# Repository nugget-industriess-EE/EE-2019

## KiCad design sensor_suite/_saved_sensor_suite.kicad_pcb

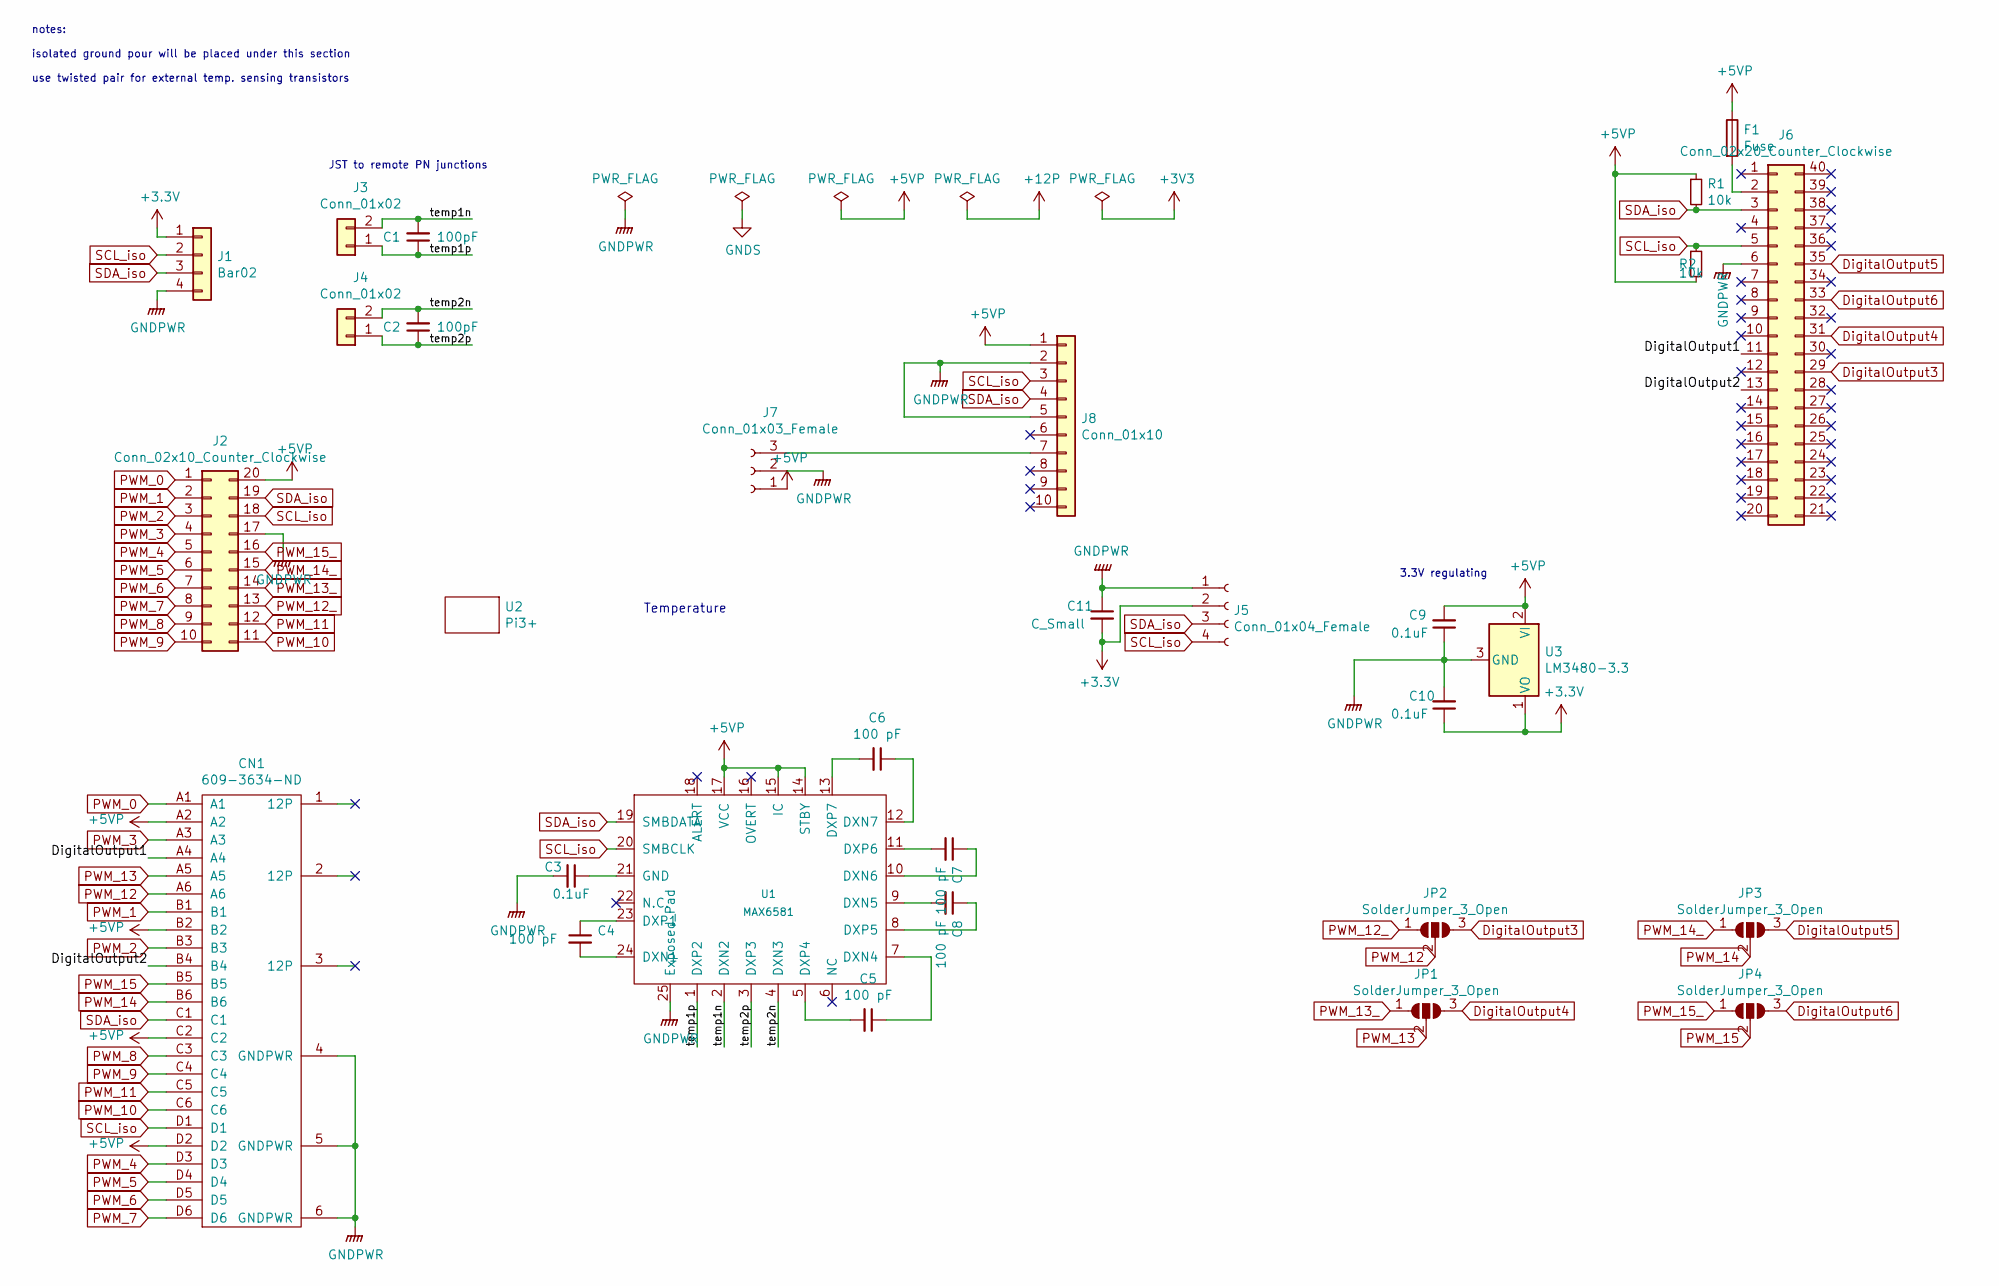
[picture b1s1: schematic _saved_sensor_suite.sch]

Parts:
C1, C2: 100pF; C_0805_2012Metric_Pad1.15x1.40mm_HandSolder
C3, C9, C10: 0.1uF; C_0805_2012Metric_Pad1.15x1.40mm_HandSolder
C4, C5, C6, C7, C8: 100 pF; C_0805_2012Metric_Pad1.15x1.40mm_HandSolder
C11: C_Small; C_0805_2012Metric_Pad1.15x1.40mm_HandSolder
CN1: 609-3634-ND
F1: Fuse; Fuse_1812_4532Metric_Pad1.30x3.40mm_HandSolder
J1: Bar02; PinHeader_1x04_P2.54mm_Vertical
J2: Conn_02x10_Counter_Clockwise; PCA9685
J3, J4: Conn_01x02; JST_EH_B02B-EH-A_1x02_P2.50mm_Vertical
J5: Conn_01x04_Female; PinHeader_1x04_P2.54mm_Vertical
J6: Conn_02x20_Counter_Clockwise; PinHeader_2x20_P2.54mm_Vertical
J7: Conn_01x03_Female; JST_EH_B03B-EH-A_1x03_P2.50mm_Vertical
J8: Conn_01x10; PinHeader_1x10_P2.54mm_Vertical
JP1, JP2, JP3, JP4: SolderJumper_3_Open; SolderJumper-3_P1.3mm_Open_RoundedPad1.0x1.5mm_NumberLabels
R1, R2: 10k; R_0805_2012Metric_Pad1.15x1.40mm_HandSolder
U1: MAX6581; QFN-24-1EP_4x4mm_P0.5mm_EP2.7x2.7mm
U2: Pi3+
U3: LM3480-3.3; SOT-23

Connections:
+3V3: C10.1, C11.2, J1.1, J5.2, U3.1 (VO)
+5VP: C9.2, CN1.A2, CN1.B2, CN1.C2, CN1.D2, F1.1, J2.20, J7.1, J8.1, R1.1, R2.2, U1.14 (STBY), U1.15 (IC), U1.17 (VCC), U3.2 (VI)
/DigitalOutput1: CN1.A4, J6.11
/DigitalOutput2: CN1.B4, J6.13
/temp1n: C1.2, J3.2, U1.2 (DXN2)
/temp1p: C1.1, J3.1, U1.1 (DXP2)
/temp2n: C2.2, J4.2, U1.4 (DXN3)
/temp2p: C2.1, J4.1, U1.3 (DXP3)
DigitalOutput3: J6.29, JP2.3 (B)
DigitalOutput4: J6.31, JP1.3 (B)
DigitalOutput5: J6.35, JP3.3 (B)
DigitalOutput6: J6.33, JP4.3 (B)
GNDPWR: C3.2, C9.1, C10.2, C11.1, CN1.4 (GNDPWR), CN1.5 (GNDPWR), CN1.6 (GNDPWR), J1.4, J2.17, J5.1, J6.6, J7.2, J8.2, J8.5, U1.25 (Exposed_Pad), U3.3 (GND)
unnamed: C3.1, U1.21 (GND)
unnamed: C4.1, U1.23 (DXP1)
unnamed: C4.2, U1.24 (DXN1)
unnamed: C5.1, U1.7 (DXN4)
unnamed: C5.2, U1.5 (DXP4)
unnamed: C6.1, U1.12 (DXN7)
unnamed: C6.2, U1.13 (DXP7)
unnamed: C7.1, U1.10 (DXN6)
unnamed: C7.2, U1.11 (DXP6)
unnamed: C8.1, U1.8 (DXP5)
unnamed: C8.2, U1.9 (DXN5)
unnamed: F1.2, J6.2
unnamed: J7.3, J8.7
PWM_0: CN1.A1, J2.1
PWM_1: CN1.B1, J2.2
PWM_2: CN1.B3, J2.3
PWM_3: CN1.A3, J2.4
PWM_4: CN1.D3, J2.5
PWM_5: CN1.D4, J2.6
PWM_6: CN1.D5, J2.7
PWM_7: CN1.D6, J2.8
PWM_8: CN1.C3, J2.9
PWM_9: CN1.C4, J2.10
PWM_10: CN1.C6, J2.11
PWM_11: CN1.C5, J2.12
PWM_12: CN1.A6, JP2.2 (C)
PWM_12_: J2.13, JP2.1 (A)
PWM_13: CN1.A5, JP1.2 (C)
PWM_13_: J2.14, JP1.1 (A)
PWM_14: CN1.B6, JP3.2 (C)
PWM_14_: J2.15, JP3.1 (A)
PWM_15: CN1.B5, JP4.2 (C)
PWM_15_: J2.16, JP4.1 (A)
SCL_iso: CN1.D1, J1.2, J2.18, J5.4, J6.5, J8.3, R2.1, U1.20 (SMBCLK)
SDA_iso: CN1.C1, J1.3, J2.19, J5.3, J6.3, J8.4, R1.2, U1.19 (SMBDATA)

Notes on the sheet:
JST to remote PN junctions
3.3V regulating
notes: isolated ground pour will be placed under this section use twisted pair for external temp. sensing transistors
Temperature

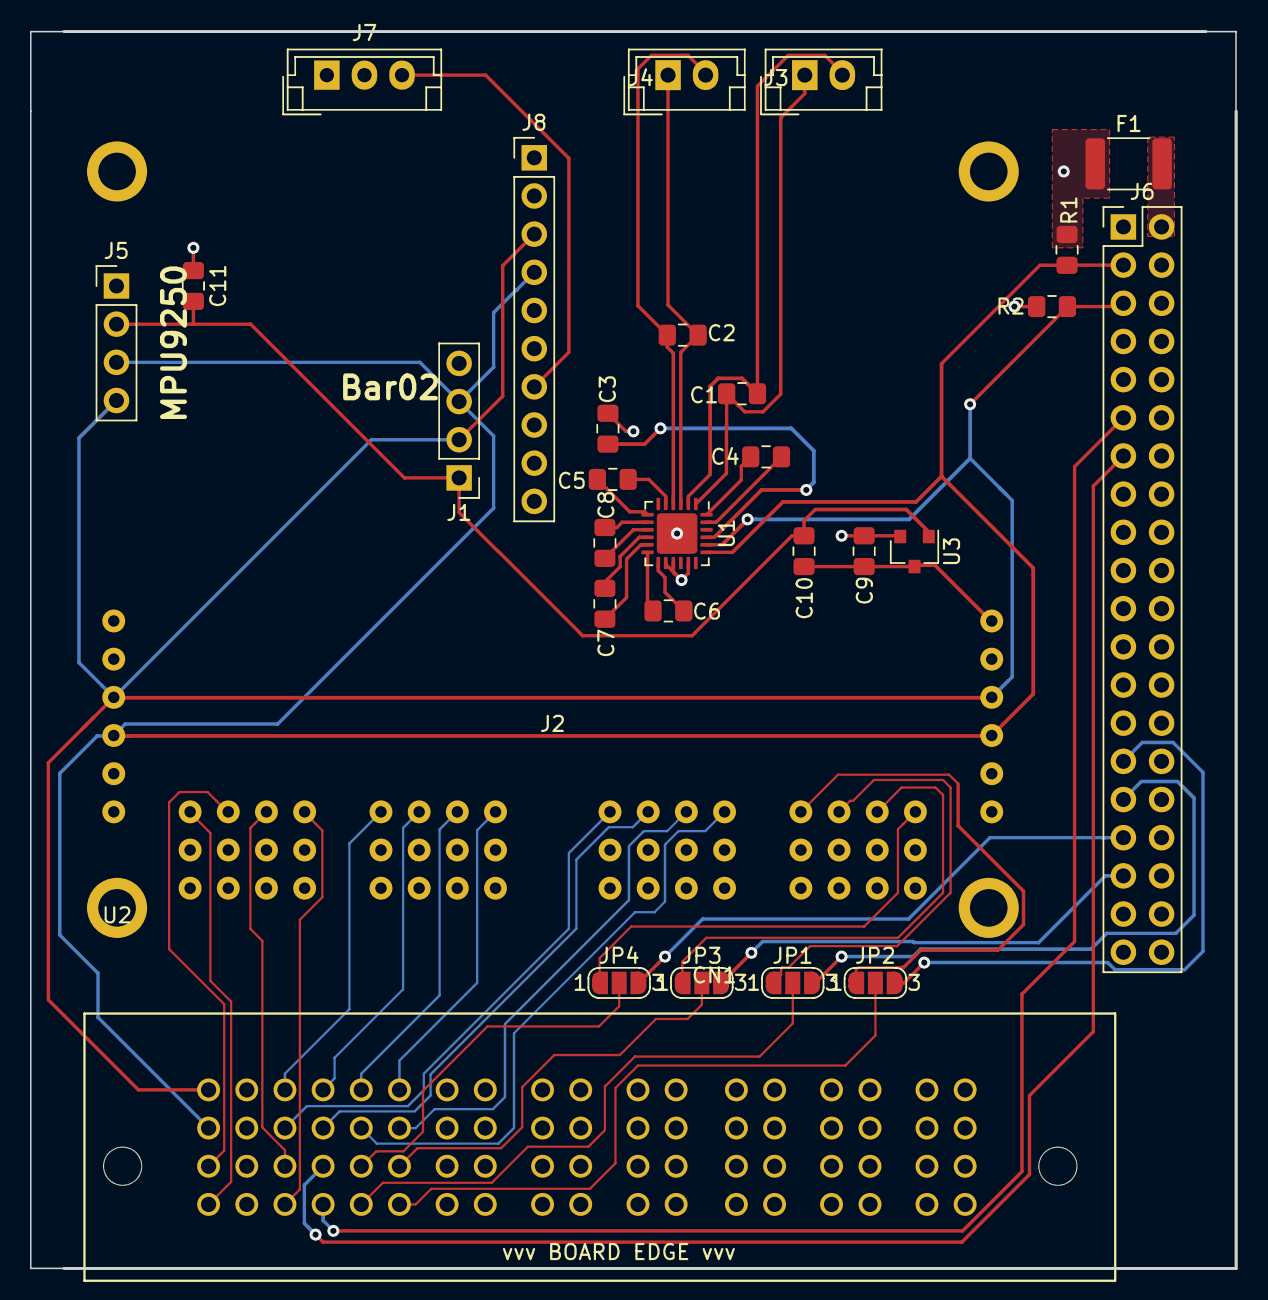
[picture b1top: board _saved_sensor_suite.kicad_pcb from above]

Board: 4 copper layers, 80.2 x 82.3 mm, 30 parts (0 on the bottom side), 48 nets.

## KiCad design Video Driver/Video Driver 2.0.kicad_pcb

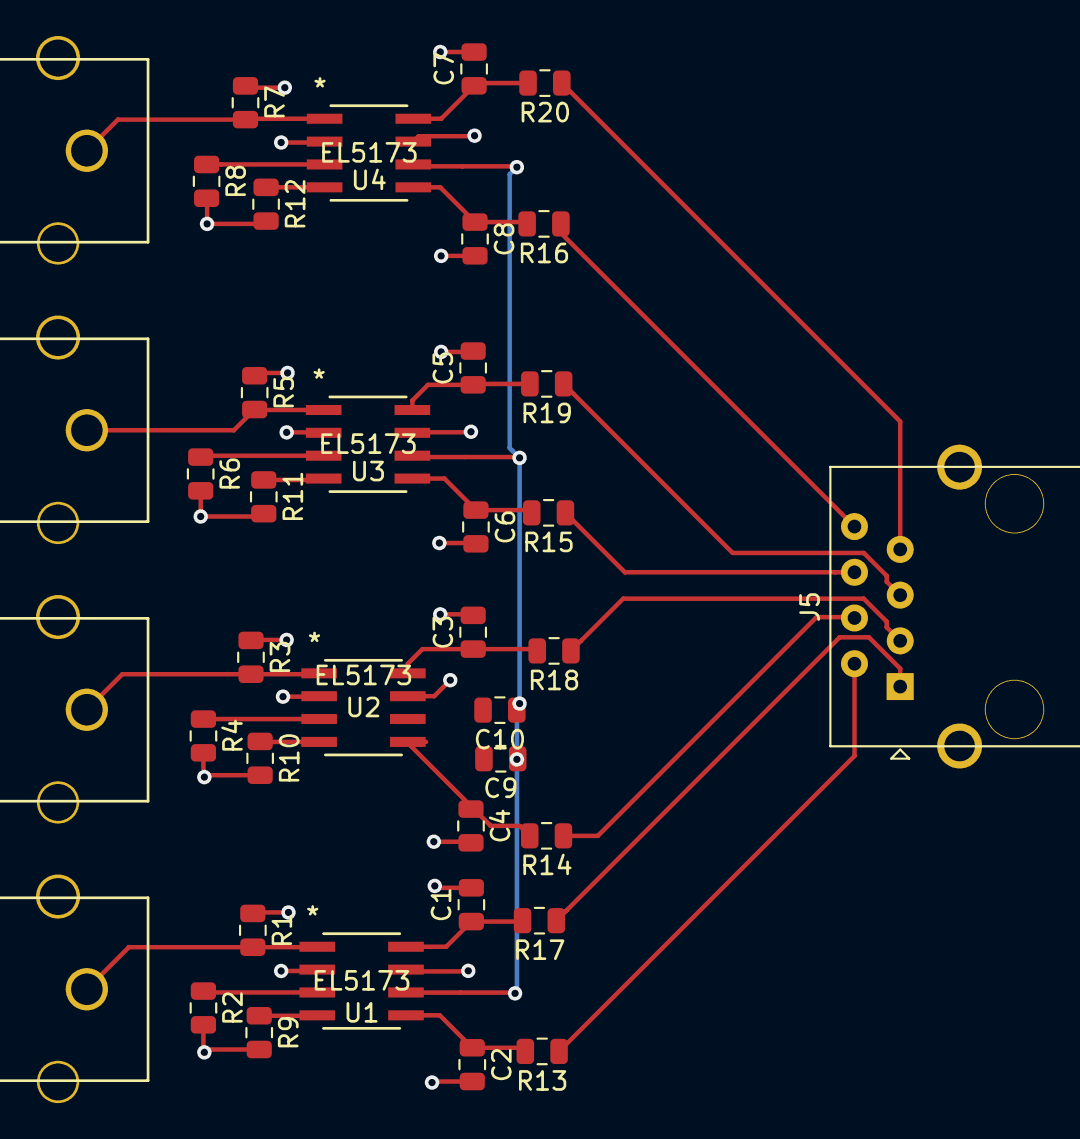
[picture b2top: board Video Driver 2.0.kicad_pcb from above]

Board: 2 copper layers, 39 parts (0 on the bottom side), 30 nets.

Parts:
C1, C2, C3, C4, C5, C6, C7, C8: 1 pF; C_0805_2012Metric
C9: 4.7 uF; C_0805_2012Metric
C10: 0.1 uF; C_0805_2012Metric
J1, J2, J3, J4: Conn_01x01; RCA_Jack
J5: RJ45; RJ45_Amphenol_54602-x08_Horizontal
R1, R2, R3, R4, R5, R6, R7, R8, R9, R10, R11, R12, R13, R14, R15, R16, R17, R18, R19, R20: 50; R_0805_2012Metric
U1, U2, U3, U4: EL5173; EL5173ISZ

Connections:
+5V: C9.1, C10.1, U1.6, U2.6, U3.6, U4.6
GND: C1.2, C2.2, C3.2, C4.2, C5.2, C6.2, C7.2, C8.2, C9.2, C10.2, R1.1, R2.2, R3.1, R4.2, R5.1, R6.2, R7.1, R8.2, R9.2, R10.2, R11.2, R12.2, U1.2, U1.7, U2.2, U2.7, U3.2, U3.7, U4.2, U4.7
unnamed: C1.1, R17.2, U1.8
unnamed: C2.1, R13.2, U1.5
unnamed: C3.1, R18.2, U2.8
unnamed: C4.1, R14.2, U2.5
unnamed: C5.1, R19.2, U3.8
unnamed: C6.1, R15.2, U3.5
unnamed: C7.1, R20.2, U4.8
unnamed: C8.1, R16.2, U4.5
unnamed: J1.1, R3.2, U2.1
unnamed: J2.1, R5.2, U3.1
unnamed: J3.1, R1.2, U1.1
unnamed: J4.1, R7.2, U4.1
unnamed: J5.1, R17.1
unnamed: J5.2, R13.1
unnamed: J5.3, R18.1
unnamed: J5.4, R14.1
unnamed: J5.5, R19.1
unnamed: J5.6, R15.1
unnamed: J5.7, R20.1
unnamed: J5.8, R16.1
unnamed: R2.1, U1.3
unnamed: R4.1, U2.3
unnamed: R6.1, U3.3
unnamed: R8.1, U4.3
unnamed: R9.1, U1.4
unnamed: R10.1, U2.4
unnamed: R11.1, U3.4
unnamed: R12.1, U4.4

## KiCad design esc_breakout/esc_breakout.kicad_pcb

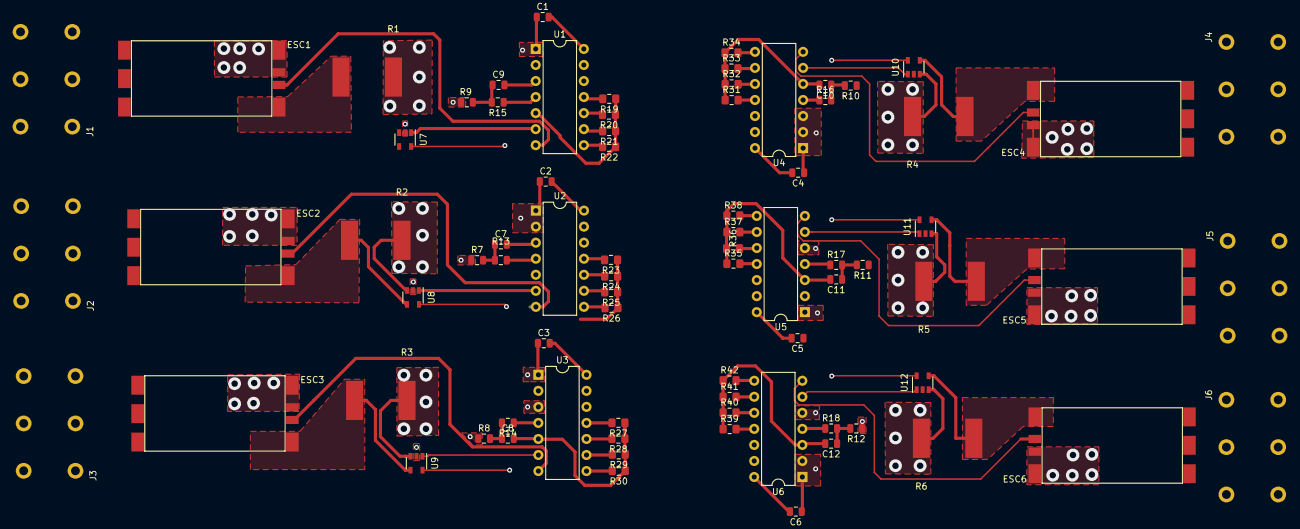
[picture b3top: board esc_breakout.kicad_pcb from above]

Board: 4 copper layers, 78 parts (0 on the bottom side), 75 nets.

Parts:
C1, C2, C3, C4, C5, C6: .1uF; C_0805_2012Metric
C7, C8, C9, C10, C11, C12: 10nF; C_0805_2012Metric
ESC1, ESC2, ESC3, ESC4, ESC5, ESC6: ESC
J1, J2, J3, J4, J5, J6: Conn_01x03_Female; Wago Terminal Blocks
R1, R2, R3, R4, R5, R6: WSLP59311L000FEB; Shunt Resistor
R7, R8, R9, R10, R11, R12: 10k; R_0805_2012Metric
R13, R14, R15, R16, R17, R18: 100; R_0805_2012Metric
R19, R20, R21, R22, R24, R25, R26, R28, R29, R30, R36, R37, R38, R40, R41, R42: 1k; R_0805_2012Metric_Pad1.15x1.40mm_HandSolder
R23, R27, R31, R32, R33, R34, R35, R39: R_Small; R_0805_2012Metric_Pad1.15x1.40mm_HandSolder
U1, U2, U3, U4, U5, U6: PIC16F15323; DIP-14_W7.62mm
U7, U8, U9, U10, U11, U12: TSC888; SOT-23-5

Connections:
+5VP: C1.1, C2.1, C3.1, C4.1, C5.1, C6.1, R7.1, R8.1, R9.1, R10.1, R11.1, R12.1, U1.1, U2.1, U2.2, U3.1, U3.3, U4.1, U4.2, U4.3, U5.1, U5.5, U6.1, U6.2, U6.5, U7.5, U8.5, U9.5, U10.5, U11.5, U12.5
+12P: R1.1, R2.1, R3.1, R4.1, R5.1, R6.1, U7.3, U8.3, U9.3, U10.3, U11.3, U12.3
/CS1: U1.6, U7.1
/CS2: U2.6, U8.1
/CS3: U3.6, U9.1
/CS4: U4.6, U10.1
/CS5: U5.6, U11.1
/CS6: U6.6, U12.1
/PWM1: ESC1.2, U1.7
/PWM2: ESC2.2, U2.7
/PWM3: ESC3.2, U3.7
/PWM4: ESC4.2, U4.7
/PWM5: ESC5.2, U5.7
/PWM6: ESC6.2, U6.7
GNDPWR: C1.2, C2.2, C3.2, C4.2, C5.2, C6.2, C7.2, C8.2, C9.2, C10.2, C11.2, C12.2, ESC1.3, ESC1.4, ESC2.3, ESC2.4, ESC3.3, ESC3.4, ESC4.3, ESC4.4, ESC5.3, ESC5.4, ESC6.3, ESC6.4, R19.1, R20.1, R21.1, R22.1, R23.1, R24.1, R25.1, R26.1, R27.1, R28.1, R29.1, R30.1, R31.1, R32.1, R33.1, R34.1, R35.1, R36.1, R37.1, R38.1, R39.1, R40.1, R41.1, R42.1, U1.2, U1.3, U1.5, U1.14, U2.3, U2.5, U2.14, U3.2, U3.5, U3.14, U4.5, U4.14, U5.2, U5.3, U5.14, U6.3, U6.14, U7.2, U8.2, U9.2, U10.2, U11.2, U12.2
unnamed: C7.1, R7.2, R13.2
unnamed: C8.1, R8.2, R14.2
unnamed: C9.1, R9.2, R15.2
unnamed: C10.1, R10.2, R16.2
unnamed: C11.1, R11.2, R17.2
unnamed: C12.1, R12.2, R18.2
unnamed: ESC1.1, R1.2, U7.4
unnamed: ESC1.5, J1.1
unnamed: ESC1.6, J1.2
unnamed: ESC1.7, J1.3
unnamed: ESC2.1, R2.2, U8.4
unnamed: ESC2.5, J2.1
unnamed: ESC2.6, J2.2
unnamed: ESC2.7, J2.3
unnamed: ESC3.1, R3.2, U9.4
unnamed: ESC3.5, J3.1
unnamed: ESC3.6, J3.2
unnamed: ESC3.7, J3.3
unnamed: ESC4.1, R4.2, U10.4
unnamed: ESC4.5, J4.1
unnamed: ESC4.6, J4.2
unnamed: ESC4.7, J4.3
unnamed: ESC5.1, R5.2, U11.4
unnamed: ESC5.5, J5.1
unnamed: ESC5.6, J5.2
unnamed: ESC5.7, J5.3
unnamed: ESC6.1, R6.2, U12.4
unnamed: ESC6.5, J6.1
unnamed: ESC6.6, J6.2
unnamed: ESC6.7, J6.3
unnamed: R13.1, U2.4
unnamed: R14.1, U3.4
unnamed: R15.1, U1.4
unnamed: R16.1, U4.4
unnamed: R17.1, U5.4
unnamed: R18.1, U6.4
unnamed: R19.2, U1.11
unnamed: R20.2, U1.10
unnamed: R21.2, U1.9
unnamed: R22.2, U1.8
unnamed: R23.2, U2.11
unnamed: R24.2, U2.10
unnamed: R25.2, U2.9
unnamed: R26.2, U2.8
unnamed: R27.2, U3.11
unnamed: R28.2, U3.10
unnamed: R29.2, U3.9
unnamed: R30.2, U3.8
unnamed: R31.2, U4.11
unnamed: R32.2, U4.10
unnamed: R33.2, U4.9
unnamed: R34.2, U4.8
unnamed: R35.2, U5.11
unnamed: R36.2, U5.10
unnamed: R37.2, U5.9
unnamed: R38.2, U5.8
unnamed: R39.2, U6.11
unnamed: R40.2, U6.10
unnamed: R41.2, U6.9
unnamed: R42.2, U6.8

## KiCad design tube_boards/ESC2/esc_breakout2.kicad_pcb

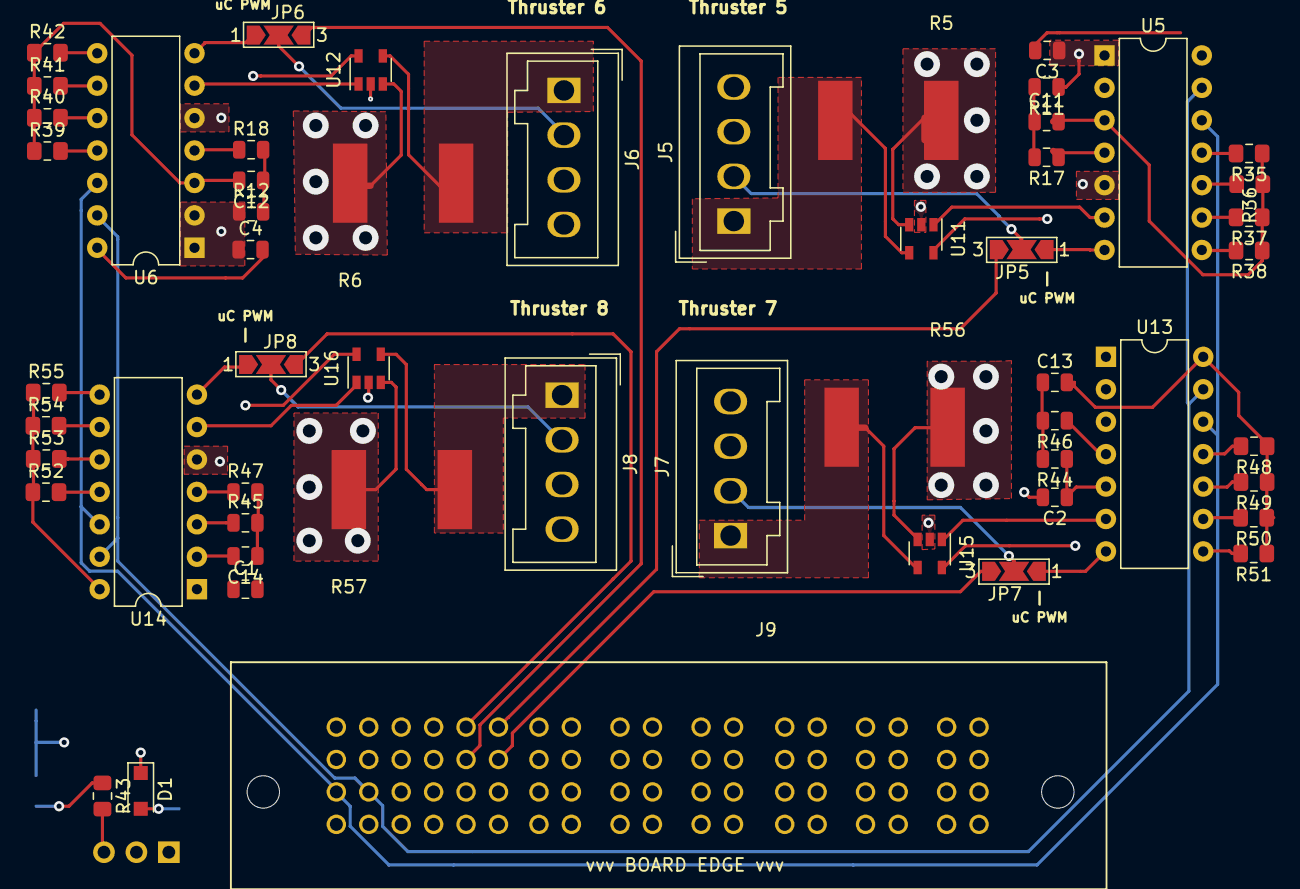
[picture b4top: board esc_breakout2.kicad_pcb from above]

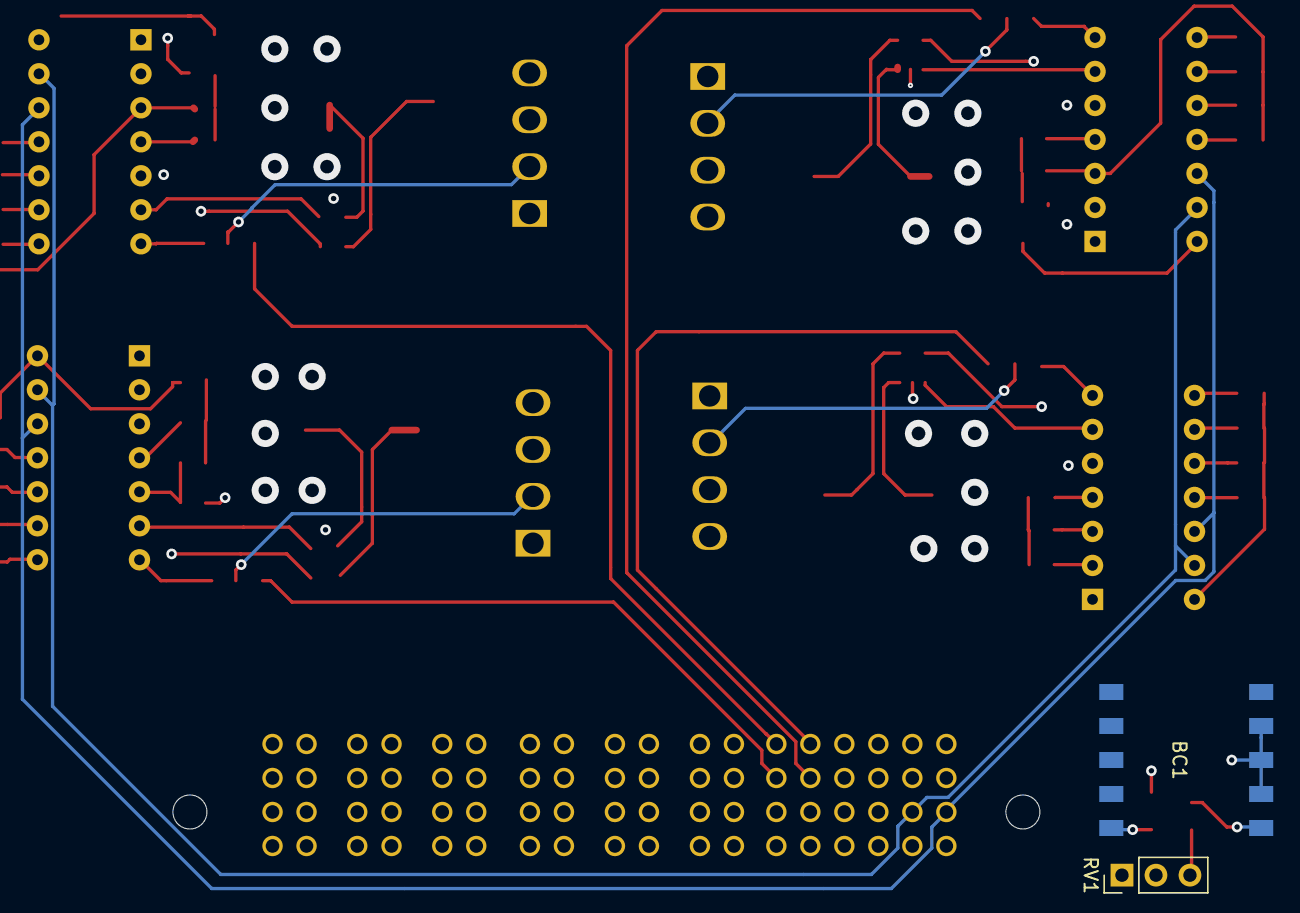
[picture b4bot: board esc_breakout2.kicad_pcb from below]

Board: 4 copper layers, 57 parts (2 on the bottom side), 52 nets.

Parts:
BC1: R-78AA-1.0; R78AA-1.0
C1, C2, C3, C4: .1uF; C_0805_2012Metric
C11, C12, C13, C14: 10nF; C_0805_2012Metric
D1: D_Small; D_SOD-123F
J5, J6, J7, J8: Conn_01x04_Female; Wago_734-134_1x04_P3.50mm_Vertical
J9: Conn_02x36_Top_Bottom; 609-3634-ND
JP5, JP6, JP7, JP8: SolderJumper_3_Open; SolderJumper-3_P2.0mm_Open_TrianglePad1.0x1.5mm_NumberLabels
R5, R6, R56, R57: WSLP59311L000FEB; Shunt Resistor
R11, R12, R44, R45: 10k; R_0805_2012Metric
R17, R18, R46, R47: 100; R_0805_2012Metric
R35, R39, R48, R52: R_Small; R_0805_2012Metric_Pad1.15x1.40mm_HandSolder
R36, R37, R38, R40, R41, R42, R49, R50, R51, R53, R54, R55: 1k; R_0805_2012Metric_Pad1.15x1.40mm_HandSolder
R43: R_Small; R_0805_SMD
RV1: R_POT_TRIM_US; PinHeader_1x03_P2.54mm_Vertical
U5, U6, U13, U14: PIC16F15323; DIP-14_W7.62mm
U11, U12, U15, U16: TSC888; SOT-23-5

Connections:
+5VP: C1.1, C2.1, C3.1, C4.1, D1.1, R11.1, R12.1, R44.1, R45.1, U5.1, U5.5, U6.1, U6.2, U6.5, U11.5, U12.5, U13.1, U13.2, U13.3, U13.5, U14.1, U14.3, U14.5, U15.5, U16.5
+12P: BC1.1, BC1.2, BC1.10, J9.1, J9.2, J9.3, R5.1, R6.1, R56.1, R57.1, U11.3, U12.3, U15.3, U16.3
/CS5: U5.6, U11.1
/CS6: U6.6, U12.1
/CS7: U13.6, U15.1
/CS8: U14.6, U16.1
/PCA_PWM5: J9.D6, JP5.3
/PCA_PWM6: J9.C5, JP6.3
/PCA_PWM7: J9.C6, JP7.3
/PCA_PWM8: J9.D5, JP8.3
/PWM5: JP5.1, U5.7
/PWM6: JP6.1, U6.7
/PWM7: JP7.1, U13.7
/PWM8: JP8.1, U14.7
/SCL_iso: J9.B1, U5.12, U6.12, U13.12, U14.12
/SDA_iso: J9.B2, U5.13, U6.13, U13.13, U14.13
GNDPWR: BC1.3, BC1.7, BC1.8, BC1.9, C1.2, C2.2, C3.2, C4.2, C11.2, C12.2, C13.2, C14.2, J5.3, J5.4, J6.3, J6.4, J7.3, J7.4, J8.3, J8.4, J9.4, J9.5, J9.6, R35.1, R36.1, R37.1, R38.1, R39.1, R40.1, R41.1, R42.1, R48.1, R49.1, R50.1, R51.1, R52.1, R53.1, R54.1, R55.1, RV1.1, U5.2, U5.3, U5.14, U6.3, U6.14, U11.2, U12.2, U13.14, U14.2, U14.14, U15.2, U16.2
unnamed: BC1.4, BC1.5, D1.2
unnamed: BC1.6, R43.1
unnamed: C11.1, R11.2, R17.2
unnamed: C12.1, R12.2, R18.2
unnamed: C13.1, R44.2, R46.2
unnamed: C14.1, R45.2, R47.2
unnamed: J5.1, R5.2, U11.4
unnamed: J5.2, JP5.2
unnamed: J6.1, R6.2, U12.4
unnamed: J6.2, JP6.2
unnamed: J7.1, R56.2, U15.4
unnamed: J7.2, JP7.2
unnamed: J8.1, R57.2, U16.4
unnamed: J8.2, JP8.2
unnamed: R17.1, U5.4
unnamed: R18.1, U6.4
unnamed: R35.2, U5.11
unnamed: R36.2, U5.10
unnamed: R37.2, U5.9
unnamed: R38.2, U5.8
unnamed: R39.2, U6.11
unnamed: R40.2, U6.10
unnamed: R41.2, U6.9
unnamed: R42.2, U6.8
unnamed: R43.2, RV1.2, RV1.3
unnamed: R46.1, U13.4
unnamed: R47.1, U14.4
unnamed: R48.2, U13.11
unnamed: R49.2, U13.10
unnamed: R50.2, U13.9
unnamed: R51.2, U13.8
unnamed: R52.2, U14.11
unnamed: R53.2, U14.10
unnamed: R54.2, U14.9
unnamed: R55.2, U14.8

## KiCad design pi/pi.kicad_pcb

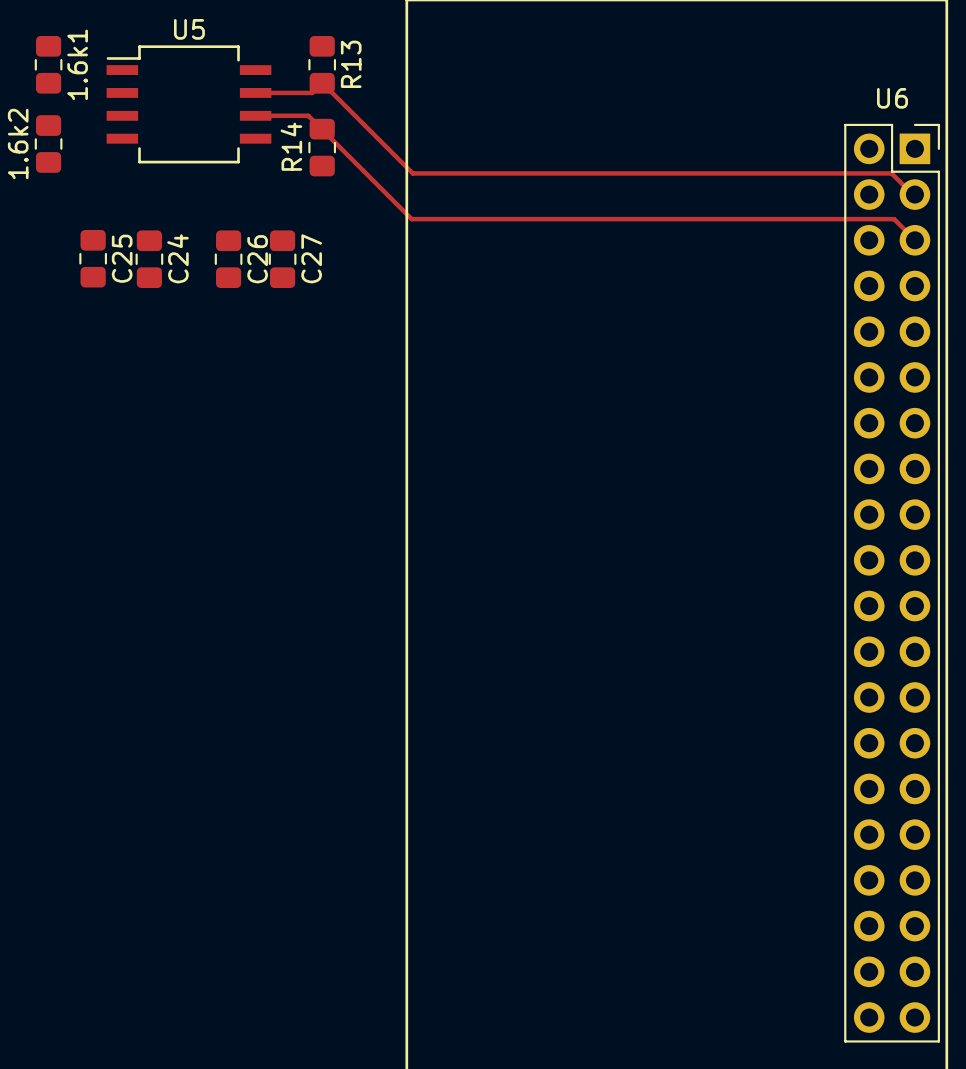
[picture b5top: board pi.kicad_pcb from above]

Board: 2 copper layers, 10 parts (0 on the bottom side), 9 nets.

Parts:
1.6k1, 1.6k2: R_Small; R_0805_2012Metric_Pad1.15x1.40mm_HandSolder
C24, C26: 0.01u; C_0805_2012Metric_Pad1.15x1.40mm_HandSolder
C25, C27: 0.1u; C_0805_2012Metric_Pad1.15x1.40mm_HandSolder
R13, R14: 1.6k; R_0805_2012Metric_Pad1.15x1.40mm_HandSolder
U5: ADuM1250; SO-8_5.3x6.2mm_P1.27mm
U6: PI_ZERO

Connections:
5VPI: C26.1, C27.1, U6.2, U6.4
+3V3: U6.1, U6.17
+5VP: 1.6k1.1, 1.6k2.1, C24.1, C25.1, R13.1, R14.1, U5.1, U5.8
/SCL_iso: 1.6k2.2, U5.3
/SDA_iso: 1.6k1.2, U5.2
GNDPWR: C24.2, C25.2, U5.4
GNDS: C26.2, C27.2, U5.5, U6.6, U6.9, U6.14, U6.20, U6.25, U6.30, U6.34, U6.39
unnamed: R13.2, U5.7, U6.3
unnamed: R14.2, U5.6, U6.5

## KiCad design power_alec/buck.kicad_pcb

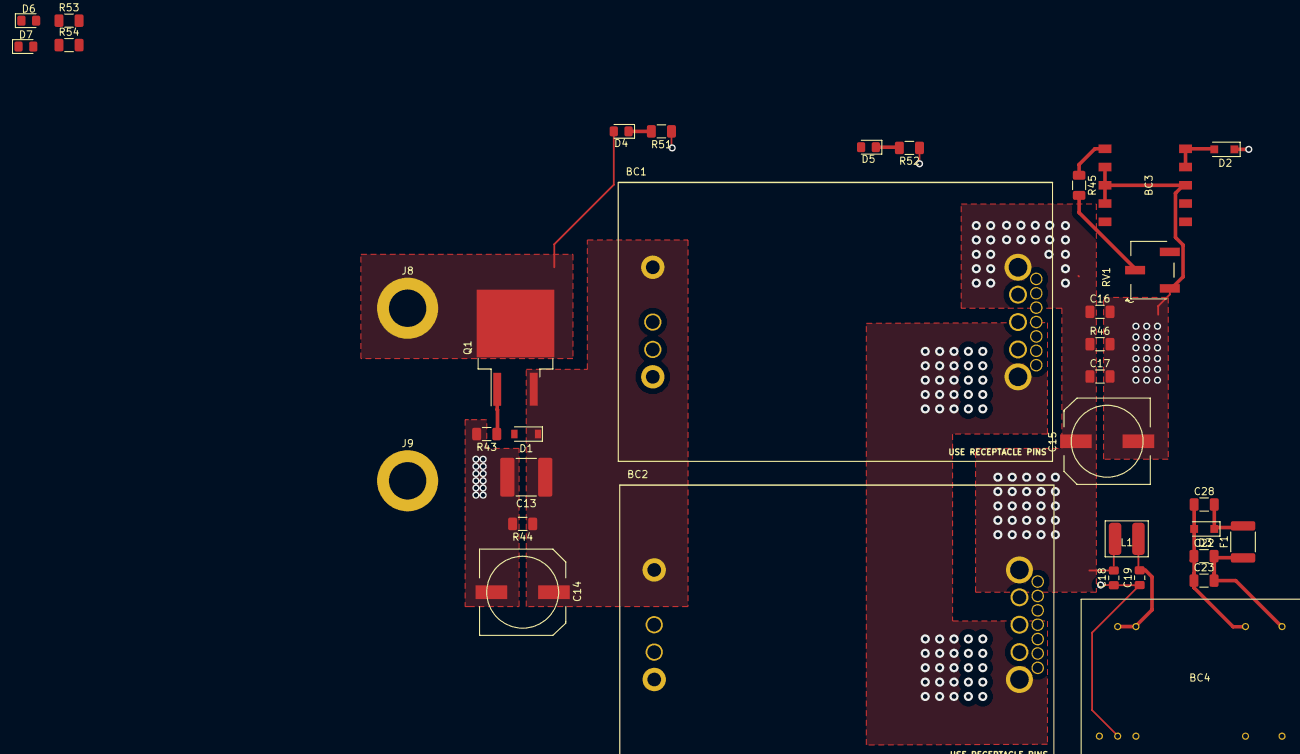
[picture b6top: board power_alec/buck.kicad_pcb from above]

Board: 4 copper layers, 35 parts (0 on the bottom side), 18 nets.

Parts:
BC1, BC2: DS_Q48SC12050NRII; DS_Q48SC12050
BC3: R-78AA-1.0; R78AA-1.0
BC4: JTF1524S05
C13: 10uF; C_2220_SMD
C14: 100uF; PCR1J101MCL1GS
C15: 330uF; PCR1J101MCL1GS
C16, C22: 10uF; C_1206_SMD
C17, C23: 1uF; C_1206_SMD
C18, C19: 2.2uF; C_0805_SMD
C28: 47uF; C_1206_SMD
D1: 12V; D_SOD-123
D2: D_Small_ALT; D_SOD-123F
D3: SMBJ5.0A-13-F; D_SOD-123F
D4, D5, D6, D7: LED; LED_0805_2012Metric_Pad1.15x1.40mm_HandSolder
F1: MF-MSMF250/16X-2; R_1812_SMD
J8, J9: Conn_01x01; 7466004
L1: 12uH; SDE0403A-120M
Q1: Q_PMOS_GDS; TO-263-2
R43: 100k; R_1206_SMD
R44: 12K; R_1206_SMD
R45: 470K; R_1206_SMD
R46: 3.3K; C_1206_SMD
R51: 2.4K; C_1206_SMD
R52, R53, R54: 600; C_1206_SMD
RV1: 200k; 3269W-1-204GLF

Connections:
5VPI: C28.2, D3.1, F1.2
+5V: BC4.14, C22.2, C23.2, D6.2, F1.1
+5VP: D2.1, D7.2
+12P: BC1.9, BC2.9, BC3.1, BC3.2, BC3.10, C15.1, C16.1, C17.1, C18.2, D5.2, L1.1, R46.1
+48V: D4.2, J8.1, Q1.2
/VIN+: BC1.1, BC2.1, C13.1, C14.1, D1.1, Q1.3, R44.1
Earth: BC1.2, BC1.4, BC2.2, BC2.4, C13.2, C14.2, J9.1, R43.2, R44.2, R51.1
GNDPWR: BC1.5, BC2.5, BC3.3, BC3.7, BC3.8, BC3.9, BC4.2, BC4.3, C15.2, C16.2, C17.2, C18.1, C19.1, R46.2, R52.1, R54.1, RV1.1
GNDS: BC4.16, C22.1, C23.1, C28.1, D3.2, R53.1
unnamed: BC3.4, BC3.5, D2.2
unnamed: BC3.6, R45.1
unnamed: BC4.22, BC4.23, C19.2, L1.2
unnamed: D1.2, Q1.1, R43.1
unnamed: D4.1, R51.2
unnamed: D5.1, R52.2
unnamed: D6.1, R53.2
unnamed: D7.1, R54.2
unnamed: R45.2, RV1.2, RV1.3

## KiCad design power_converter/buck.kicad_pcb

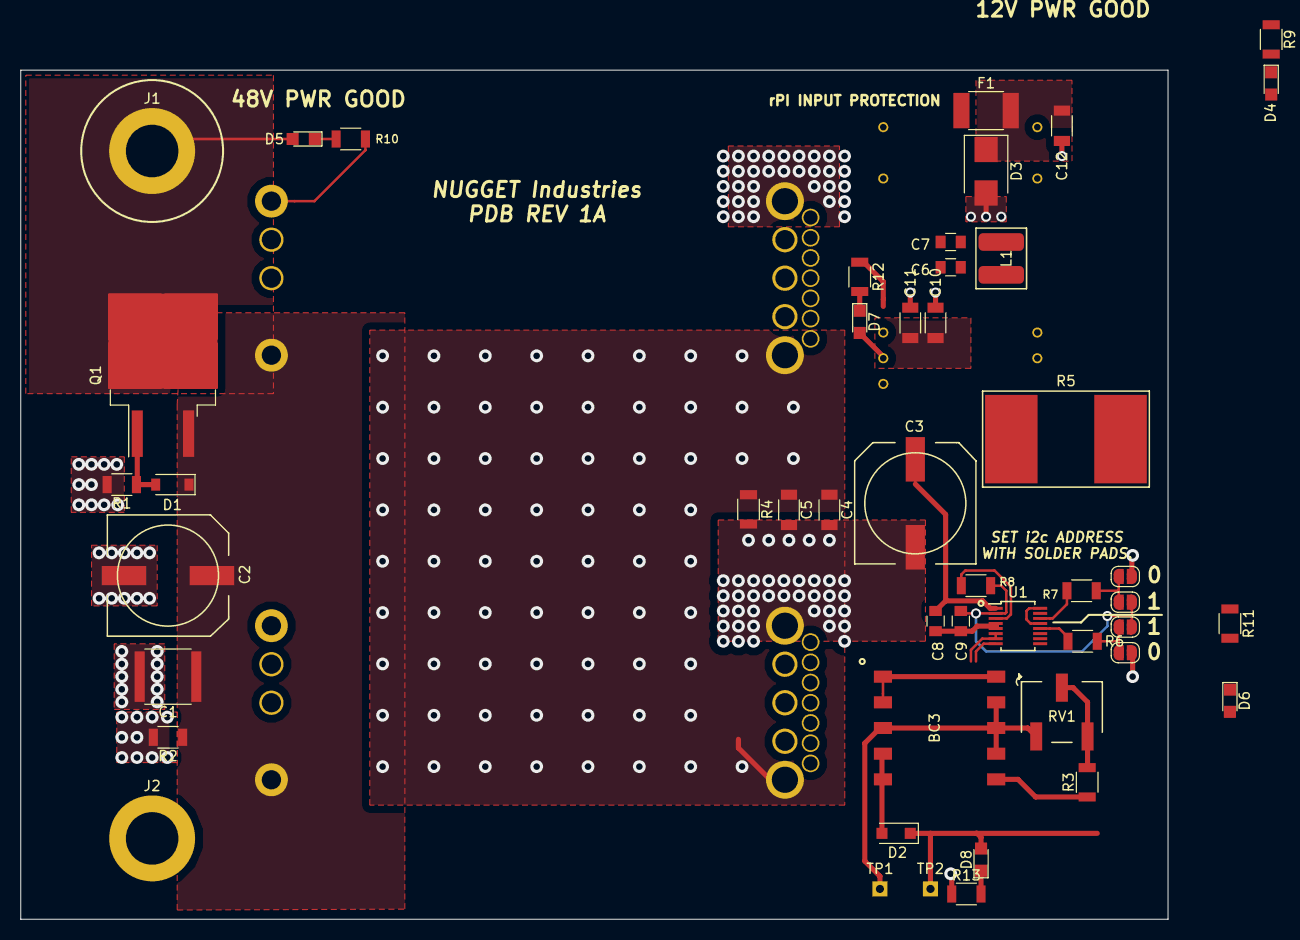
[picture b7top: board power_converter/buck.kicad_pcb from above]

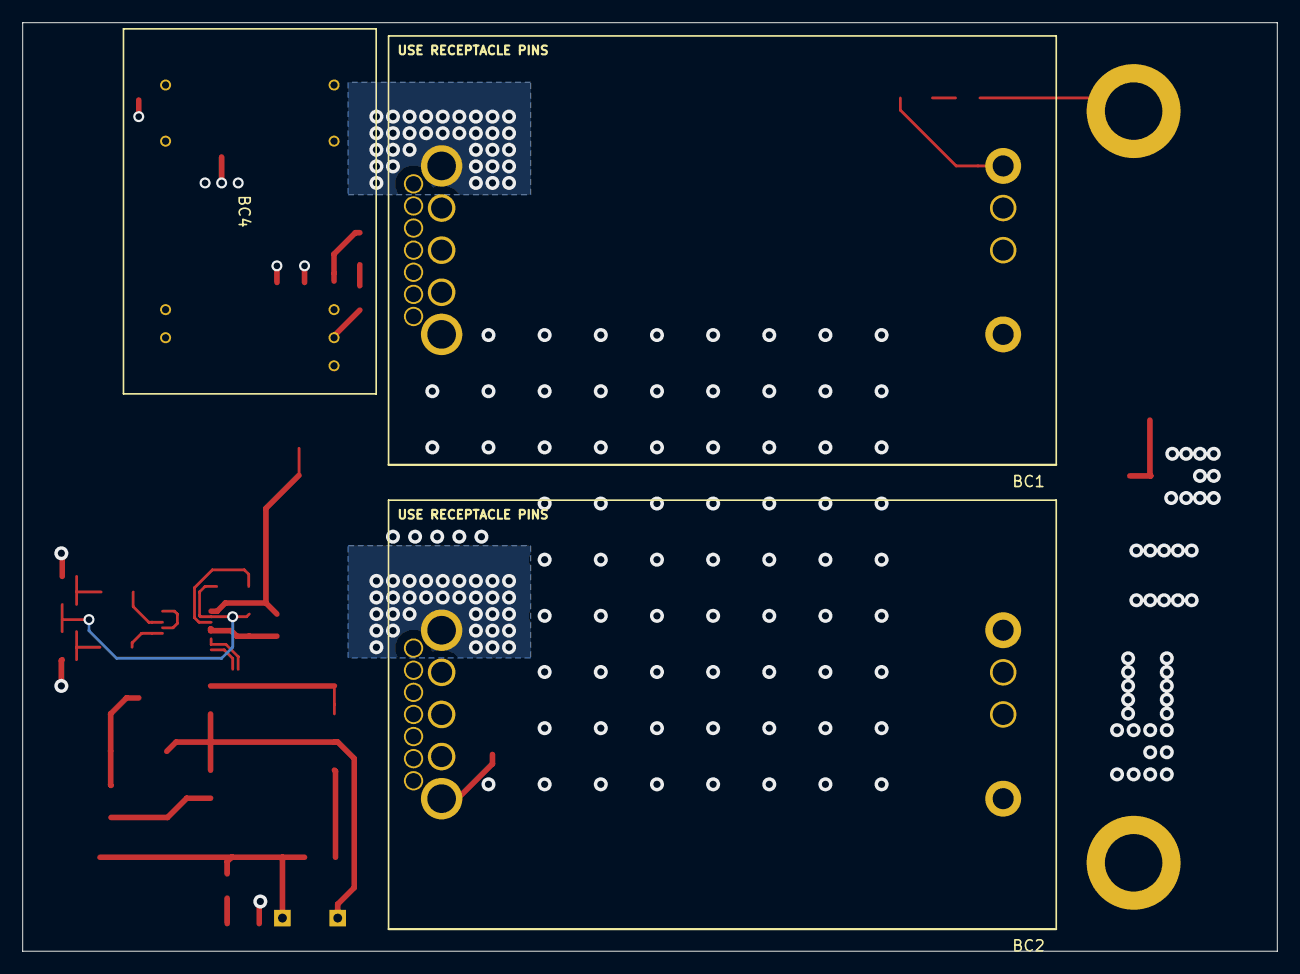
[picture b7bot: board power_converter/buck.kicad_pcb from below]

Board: 4 copper layers, 113.5 x 84.0 mm, 50 parts (3 on the bottom side), 27 nets.

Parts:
BC1, BC2: DS_Q48SC12050NRII; DS_Q48SC12050
BC3: R-78AA-1.0; R78AA-1.0
BC4: JTF1524S05
C1: 10uF; C_2220
C2: 100uF; PCR1J101MCL1GS
C3: 330uF; PCR1J101MCL1GS
C4, C10: 10uF; C_1206
C5, C11: 1uF; C_1206
C6, C7: 2.2uF; C_0805
C8, C9: .1uF; C_0805
C12: 47uF; C_1206
D1: 12V; D_SOD-123
D2: D_Small_ALT; D_SOD-123F
D3: SMBJ5.0A-13-F; D_SMB
D4, D5, D6, D7, D8: LED; LED_0805
F1: MF-MSMF250/16X-2; R_1812
J1, J2: Conn_01x01; 7466004
JP1, JP2, JP3, JP4: SolderJumper_2_Open; SolderJumper-2_P1.3mm_Open_RoundedPad1.0x1.5mm
L1: 12uH; SDE0403A-120M
Q1: Q_PMOS_GDS; TO-263-2
R1: 100K; R_1206
R2: 12K; R_1206
R3: 470K; R_1206
R4: 3.3K; R_1206
R5: WSLP59311L000FEB
R6, R7: 22K; R_1206
R8: 4.7K; R_1206
R9, R11, R12, R13: 600; R_1206
R10: 2.4K; R_1206
RV1: 200k; 3269W-1-204GLF
TP1, TP2: TestPoint; Measurement_Point_Square-TH_Small
U1: LTC2946CMS#PBF; MSOP-16_3x4mm_Pitch0.5mm

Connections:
5VPI: C12.2, D3.1, F1.2
+5V: BC4.14, C10.2, C11.2, D7.2, F1.1
+5VP: D2.1, D8.2, TP2.1
+12P: BC3.1, BC3.2, BC3.10, C6.2, L1.1, R5.2, U1.15
+48V: D5.2, J1.1, Q1.2
/ADR0: R6.1, U1.12
/ADR1: R7.1, U1.14
/GP_OUTPUT: R8.2, U1.3
/INTVCC: C9.2, JP1.1, JP3.1, R8.1, U1.2
/SDAISO: U1.6, U1.7
/VIN+: BC1.1, BC2.1, C1.1, C2.1, D1.1, Q1.3, R2.1
/VOUT: BC1.9, BC2.9, C3.1, C4.1, C5.1, C8.2, D4.2, D6.2, R4.1, R5.1, U1.1, U1.13, U1.16
Earth: BC1.2, BC1.4, BC2.2, BC2.4, C1.2, C2.2, J2.1, R1.2, R2.2, R10.1
GNDPWR: BC1.5, BC2.5, BC3.3, BC3.7, BC3.8, BC3.9, BC4.2, BC4.3, C3.2, C4.2, C5.2, C6.1, C7.1, C8.1, C9.1, JP2.1, JP4.1, R4.2, R9.1, R11.1, R13.1, RV1.1, TP1.1, U1.4, U1.5, U1.9, U1.11
GNDS: BC4.16, C10.1, C11.1, C12.1, D3.2, R12.1
unnamed: BC3.4, BC3.5, D2.2
unnamed: BC3.6, R3.1
unnamed: BC4.22, BC4.23, C7.2, L1.2
unnamed: D1.2, Q1.1, R1.1
unnamed: D4.1, R9.2
unnamed: D5.1, R10.2
unnamed: D6.1, R11.2
unnamed: D7.1, R12.2
unnamed: D8.1, R13.2
unnamed: JP1.2, JP2.2, R6.2
unnamed: JP3.2, JP4.2, R7.2
unnamed: R3.2, RV1.2, RV1.3

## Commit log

2018-12-20 All boards to date.
2018-12-21 Backplane
    Deleted full system pwer monitor
2018-12-21 Adding test file
    I added a test folder to the ee repository and want to see it works
2018-12-22 Singular ESC
    I finished the schematic for the singular esc concept
2018-12-22 PCA symbol moved to sensor board
2018-12-23 appended rov lib with standard passive component footprints
2018-12-24 not much
2019-01-08 updated library
2019-01-15 updated ESC's
2019-01-16 sensors unrouted
    nick look in "sensor suite"
2019-01-18 Sensor Board
2019-01-18 Sensor Suite
2019-01-18 commiting a tiny change on the sensor board
2019-01-22 Sensor Suite is finally buttoned up
2019-02-18 sensor board
    sensor board push
2019-02-20 Sensor Board with Video Driver
2019-02-22 Finalized sensor board for ordering
2019-03-03 Swapped out Gyro

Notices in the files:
parts and their libraries:
Copyright 2016 Accelerated Designs. All rights reserved.
